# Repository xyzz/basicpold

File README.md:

You will need an SWD programmer for initial flashing. See https://github.com/xyzz/stm32f103-keyboard-bootloader for more info.

Known issues:
- PCB-mounted stabs don't quite line up with the plate
- PCB-mounted switches don't quite line up with the plate
- The mini-USB port doesn't extend far enough and the cable is quite loose.

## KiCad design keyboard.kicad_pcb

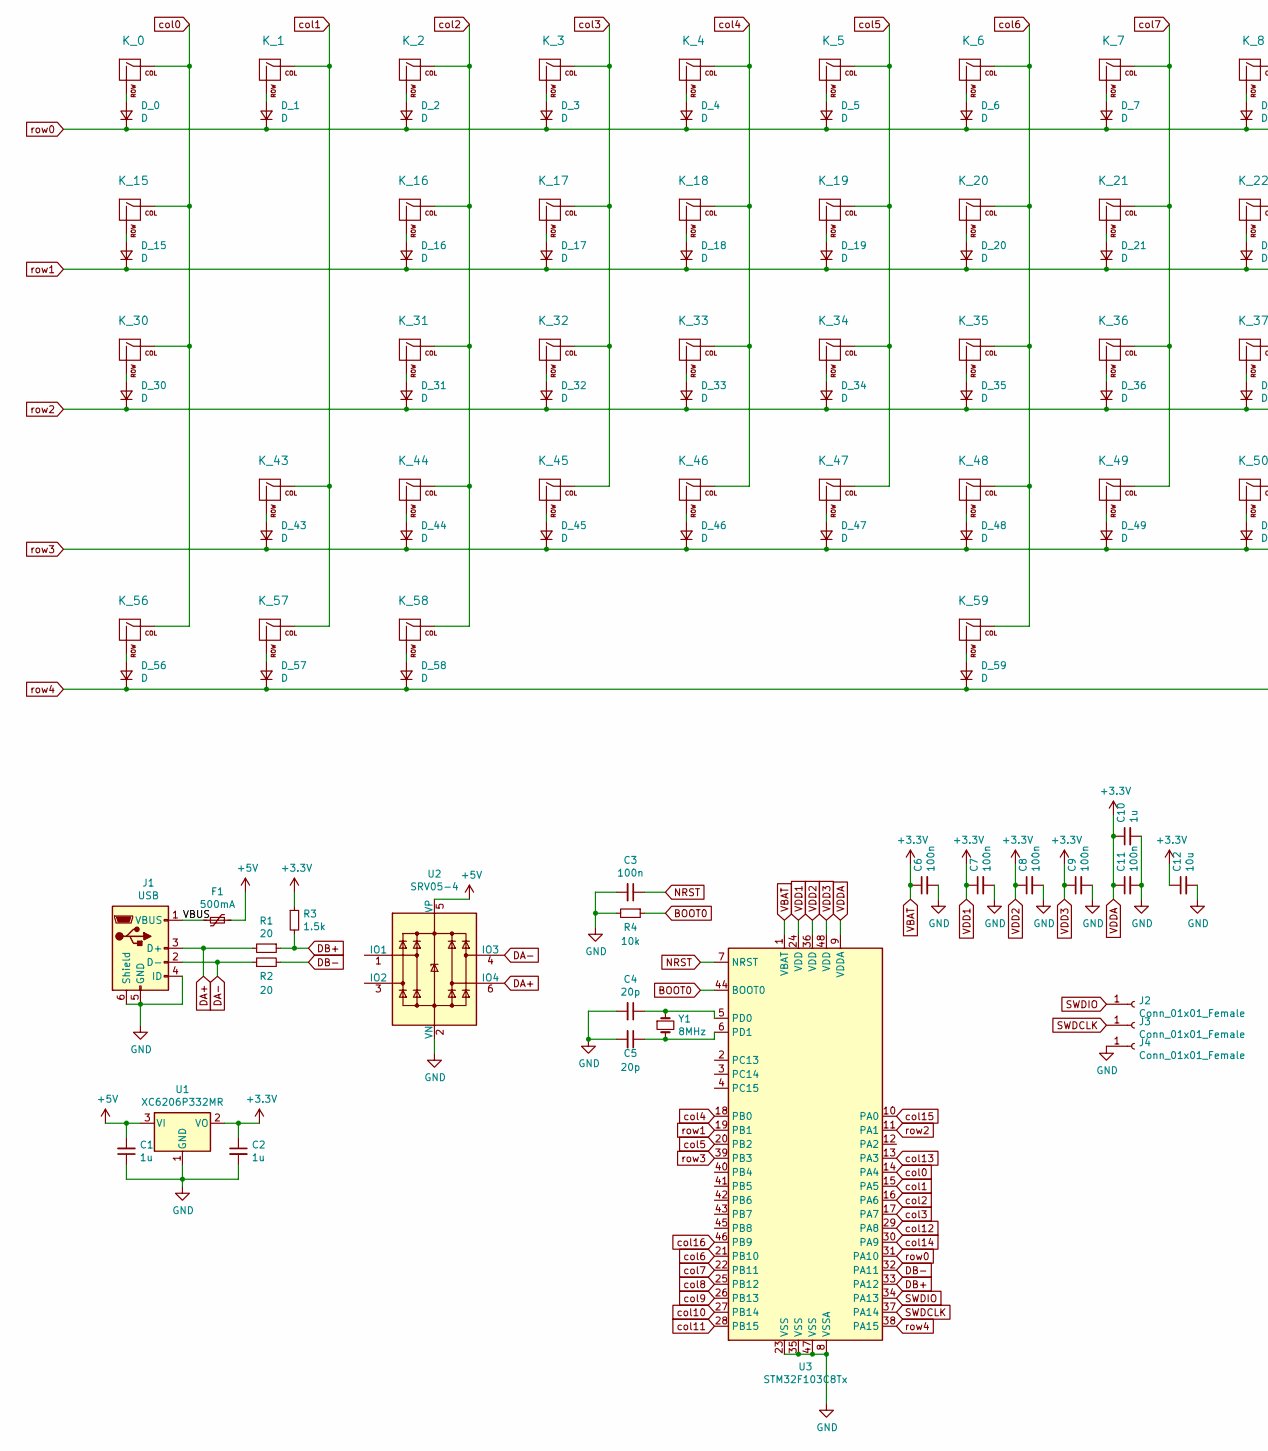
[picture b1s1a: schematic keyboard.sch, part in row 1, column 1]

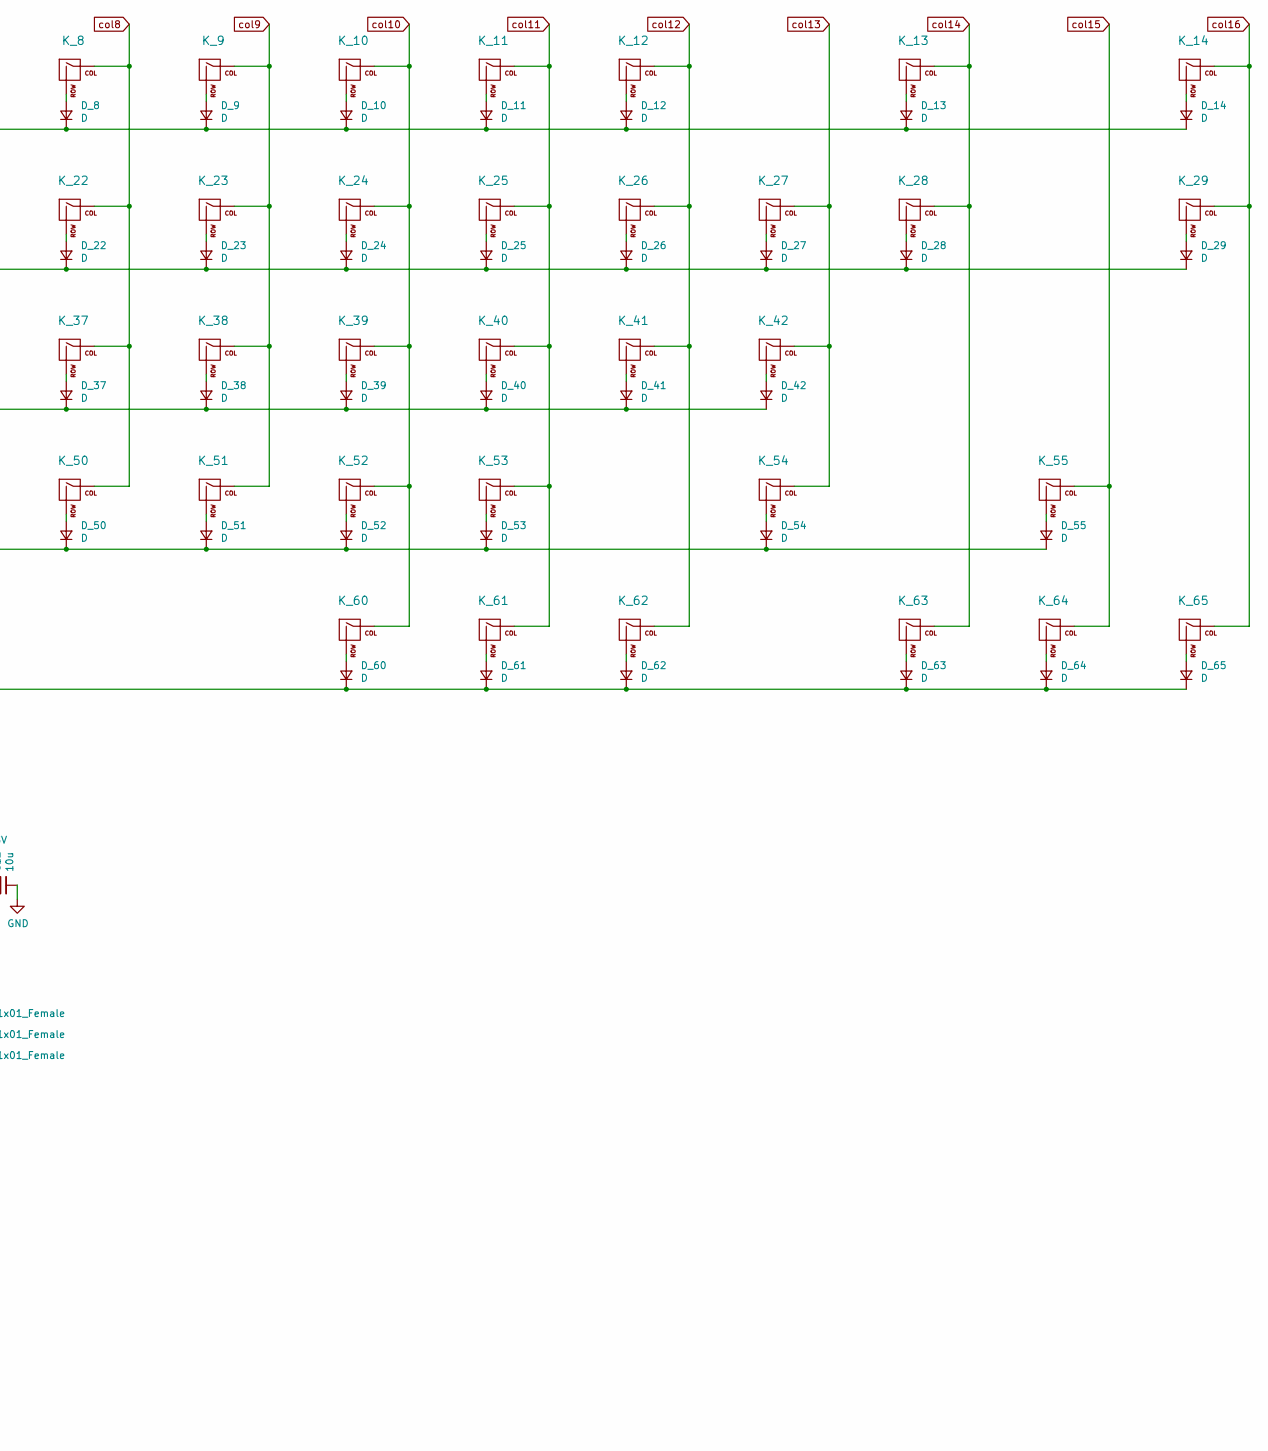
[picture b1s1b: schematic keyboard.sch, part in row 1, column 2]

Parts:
C1, C2, C10: 1u; C_0603_1608Metric; JLC C15849
C3, C6, C7, C8, C9, C11: 100n; C_0603_1608Metric; JLC C14663
C4, C5: 20p; C_0603_1608Metric; JLC C1648
C12: 10u; C_0603_1608Metric; JLC C19702
D_0, D_1, D_2, D_3, D_4, D_5, D_6, D_7, D_8, D_9, D_10, D_11, D_12, D_13, D_14, D_15, D_16, D_17, D_18, D_19, D_20, D_21, D_22, D_23, D_24, D_25, D_26, D_27, D_28, D_29, D_30, D_31, D_32, D_33, D_34, D_35, D_36, D_37, D_38, D_39, D_40, D_41, D_42, D_43, D_44, D_45, D_46, D_47, D_48, D_49, D_50, D_51, D_52, D_53, D_54, D_55, D_56, D_57, D_58, D_59, D_60, D_61, D_62, D_63, D_64, D_65: D; D_SOD-123; JLC C64898
F1: 500mA; Fuse_1206_3216Metric; JLC C369159
J1: USB; USB-Mini-B_ LCSC-C46398
J2, J3, J4: Conn_01x01_Female; TestPoint_Pad_D1.5mm
K_0, K_1, K_2, K_3, K_4, K_5, K_6, K_7, K_8, K_9, K_10, K_11, K_12, K_14, K_16, K_17, K_18, K_19, K_20, K_21, K_22, K_23, K_24, K_25, K_26, K_27, K_29, K_31, K_32, K_33, K_34, K_35, K_36, K_37, K_38, K_39, K_40, K_41, K_44, K_45, K_46, K_47, K_48, K_49, K_50, K_51, K_52, K_53, K_55, K_57, K_63, K_64, K_65: KEYSW; MXOnly-1U-NoLED
K_13: KEYSW; MXOnly-2U-NoLED
K_15, K_28: KEYSW; MXOnly-1.5U-NoLED
K_30: KEYSW; MXOnly-1.75U-NoLED
K_42, K_43, K_54: KEYSW; MXOnly-2.25U-NoLED
K_56, K_58, K_60, K_61, K_62: KEYSW; MXOnly-1.25U-NoLED
K_59: KEYSW; MXOnly-6.25U-ReversedStabilizers-NoLED
R1, R2: 20; R_0603_1608Metric; JLC C22950
R3: 1.5k; R_0603_1608Metric; JLC C22843
R4: 10k; R_0603_1608Metric; JLC C25804
U1: XC6206P332MR; SOT-23; JLC C5446
U2: SRV05-4; SOT-23-6; JLC C85364
U3: STM32F103C8Tx; LQFP-48_7x7mm_P0.5mm; JLC C8734
Y1: 8MHz; Crystal_SMD_5032-2Pin_5.0x3.2mm; JLC C115962

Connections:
+5V: C1.2, F1.1, U1.3 (VI), U2.5 (VP)
/VBUS: F1.2, J1.1 (VBUS)
BOOT0: R4.1, U3.44 (BOOT0)
DA+: J1.3 (D+), R1.2, U2.6 (IO4)
DA-: J1.2 (D-), R2.1, U2.4 (IO3)
DB+: R1.1, R3.2, U3.33 (PA12)
DB-: R2.2, U3.32 (PA11)
GND: C1.1, C2.2, C3.2, C4.2, C5.2, C6.2, C7.2, C8.2, C9.2, C10.2, C11.2, C12.2, J1.4 (ID), J1.5 (GND), J1.6 (Shield), J4.1, R4.2, U1.1 (GND), U2.2 (VN), U3.8 (VSSA), U3.23 (VSS), U3.35 (VSS), U3.47 (VSS)
NRST: C3.1, U3.7 (NRST)
unnamed: C4.1, U3.5 (PD0), Y1.1
unnamed: C5.1, U3.6 (PD1), Y1.2
unnamed: D_0.2 (A), K_0.2 (ROW)
unnamed: D_1.2 (A), K_1.2 (ROW)
unnamed: D_2.2 (A), K_2.2 (ROW)
unnamed: D_3.2 (A), K_3.2 (ROW)
unnamed: D_4.2 (A), K_4.2 (ROW)
unnamed: D_5.2 (A), K_5.2 (ROW)
unnamed: D_6.2 (A), K_6.2 (ROW)
unnamed: D_7.2 (A), K_7.2 (ROW)
unnamed: D_8.2 (A), K_8.2 (ROW)
unnamed: D_9.2 (A), K_9.2 (ROW)
unnamed: D_10.2 (A), K_10.2 (ROW)
unnamed: D_11.2 (A), K_11.2 (ROW)
unnamed: D_12.2 (A), K_12.2 (ROW)
unnamed: D_13.2 (A), K_13.2 (ROW)
unnamed: D_14.2 (A), K_14.2 (ROW)
unnamed: D_15.2 (A), K_15.2 (ROW)
unnamed: D_16.2 (A), K_16.2 (ROW)
unnamed: D_17.2 (A), K_17.2 (ROW)
unnamed: D_18.2 (A), K_18.2 (ROW)
unnamed: D_19.2 (A), K_19.2 (ROW)
unnamed: D_20.2 (A), K_20.2 (ROW)
unnamed: D_21.2 (A), K_21.2 (ROW)
unnamed: D_22.2 (A), K_22.2 (ROW)
unnamed: D_23.2 (A), K_23.2 (ROW)
unnamed: D_24.2 (A), K_24.2 (ROW)
unnamed: D_25.2 (A), K_25.2 (ROW)
unnamed: D_26.2 (A), K_26.2 (ROW)
unnamed: D_27.2 (A), K_27.2 (ROW)
unnamed: D_28.2 (A), K_28.2 (ROW)
unnamed: D_29.2 (A), K_29.2 (ROW)
unnamed: D_30.2 (A), K_30.2 (ROW)
unnamed: D_31.2 (A), K_31.2 (ROW)
unnamed: D_32.2 (A), K_32.2 (ROW)
unnamed: D_33.2 (A), K_33.2 (ROW)
unnamed: D_34.2 (A), K_34.2 (ROW)
unnamed: D_35.2 (A), K_35.2 (ROW)
unnamed: D_36.2 (A), K_36.2 (ROW)
unnamed: D_37.2 (A), K_37.2 (ROW)
unnamed: D_38.2 (A), K_38.2 (ROW)
unnamed: D_39.2 (A), K_39.2 (ROW)
unnamed: D_40.2 (A), K_40.2 (ROW)
unnamed: D_41.2 (A), K_41.2 (ROW)
unnamed: D_42.2 (A), K_42.2 (ROW)
unnamed: D_43.2 (A), K_43.2 (ROW)
unnamed: D_44.2 (A), K_44.2 (ROW)
unnamed: D_45.2 (A), K_45.2 (ROW)
unnamed: D_46.2 (A), K_46.2 (ROW)
unnamed: D_47.2 (A), K_47.2 (ROW)
unnamed: D_48.2 (A), K_48.2 (ROW)
unnamed: D_49.2 (A), K_49.2 (ROW)
unnamed: D_50.2 (A), K_50.2 (ROW)
unnamed: D_51.2 (A), K_51.2 (ROW)
unnamed: D_52.2 (A), K_52.2 (ROW)
unnamed: D_53.2 (A), K_53.2 (ROW)
unnamed: D_54.2 (A), K_54.2 (ROW)
unnamed: D_55.2 (A), K_55.2 (ROW)
unnamed: D_56.2 (A), K_56.2 (ROW)
unnamed: D_57.2 (A), K_57.2 (ROW)
unnamed: D_58.2 (A), K_58.2 (ROW)
unnamed: D_59.2 (A), K_59.2 (ROW)
unnamed: D_60.2 (A), K_60.2 (ROW)
unnamed: D_61.2 (A), K_61.2 (ROW)
unnamed: D_62.2 (A), K_62.2 (ROW)
unnamed: D_63.2 (A), K_63.2 (ROW)
unnamed: D_64.2 (A), K_64.2 (ROW)
unnamed: D_65.2 (A), K_65.2 (ROW)
SWDCLK: J3.1, U3.37 (PA14)
SWDIO: J2.1, U3.34 (PA13)
VBAT: C2.1, C6.1, C7.1, C8.1, C9.1, C10.1, C11.1, C12.1, R3.1, U1.2 (VO), U3.1 (VBAT), U3.9 (VDDA), U3.24 (VDD), U3.36 (VDD), U3.48 (VDD)
col0: K_0.1 (COL), K_15.1 (COL), K_30.1 (COL), K_56.1 (COL), U3.14 (PA4)
col1: K_1.1 (COL), K_43.1 (COL), K_57.1 (COL), U3.15 (PA5)
col2: K_2.1 (COL), K_16.1 (COL), K_31.1 (COL), K_44.1 (COL), K_58.1 (COL), U3.16 (PA6)
col3: K_3.1 (COL), K_17.1 (COL), K_32.1 (COL), K_45.1 (COL), U3.17 (PA7)
col4: K_4.1 (COL), K_18.1 (COL), K_33.1 (COL), K_46.1 (COL), U3.18 (PB0)
col5: K_5.1 (COL), K_19.1 (COL), K_34.1 (COL), K_47.1 (COL), U3.20 (PB2)
col6: K_6.1 (COL), K_20.1 (COL), K_35.1 (COL), K_48.1 (COL), K_59.1 (COL), U3.21 (PB10)
col7: K_7.1 (COL), K_21.1 (COL), K_36.1 (COL), K_49.1 (COL), U3.22 (PB11)
col8: K_8.1 (COL), K_22.1 (COL), K_37.1 (COL), K_50.1 (COL), U3.25 (PB12)
col9: K_9.1 (COL), K_23.1 (COL), K_38.1 (COL), K_51.1 (COL), U3.26 (PB13)
col10: K_10.1 (COL), K_24.1 (COL), K_39.1 (COL), K_52.1 (COL), K_60.1 (COL), U3.27 (PB14)
col11: K_11.1 (COL), K_25.1 (COL), K_40.1 (COL), K_53.1 (COL), K_61.1 (COL), U3.28 (PB15)
col12: K_12.1 (COL), K_26.1 (COL), K_41.1 (COL), K_62.1 (COL), U3.29 (PA8)
col13: K_27.1 (COL), K_42.1 (COL), K_54.1 (COL), U3.13 (PA3)
col14: K_13.1 (COL), K_28.1 (COL), K_63.1 (COL), U3.30 (PA9)
col15: K_55.1 (COL), K_64.1 (COL), U3.10 (PA0)
col16: K_14.1 (COL), K_29.1 (COL), K_65.1 (COL), U3.46 (PB9)
row0: D_0.1 (K), D_1.1 (K), D_2.1 (K), D_3.1 (K), D_4.1 (K), D_5.1 (K), D_6.1 (K), D_7.1 (K), D_8.1 (K), D_9.1 (K), D_10.1 (K), D_11.1 (K), D_12.1 (K), D_13.1 (K), D_14.1 (K), U3.31 (PA10)
row1: D_15.1 (K), D_16.1 (K), D_17.1 (K), D_18.1 (K), D_19.1 (K), D_20.1 (K), D_21.1 (K), D_22.1 (K), D_23.1 (K), D_24.1 (K), D_25.1 (K), D_26.1 (K), D_27.1 (K), D_28.1 (K), D_29.1 (K), U3.19 (PB1)
row2: D_30.1 (K), D_31.1 (K), D_32.1 (K), D_33.1 (K), D_34.1 (K), D_35.1 (K), D_36.1 (K), D_37.1 (K), D_38.1 (K), D_39.1 (K), D_40.1 (K), D_41.1 (K), D_42.1 (K), U3.11 (PA1)
row3: D_43.1 (K), D_44.1 (K), D_45.1 (K), D_46.1 (K), D_47.1 (K), D_48.1 (K), D_49.1 (K), D_50.1 (K), D_51.1 (K), D_52.1 (K), D_53.1 (K), D_54.1 (K), D_55.1 (K), U3.39 (PB3)
row4: D_56.1 (K), D_57.1 (K), D_58.1 (K), D_59.1 (K), D_60.1 (K), D_61.1 (K), D_62.1 (K), D_63.1 (K), D_64.1 (K), D_65.1 (K), U3.38 (PA15)

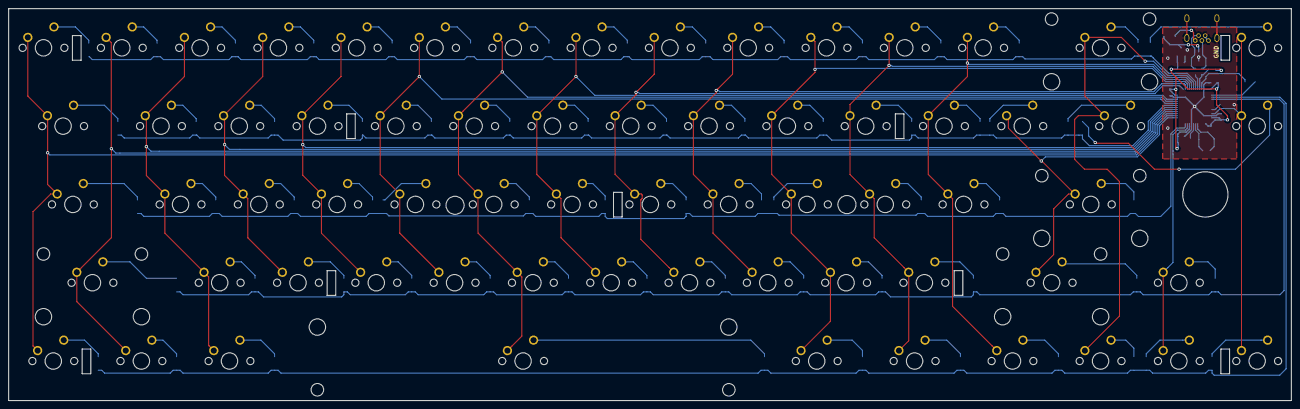
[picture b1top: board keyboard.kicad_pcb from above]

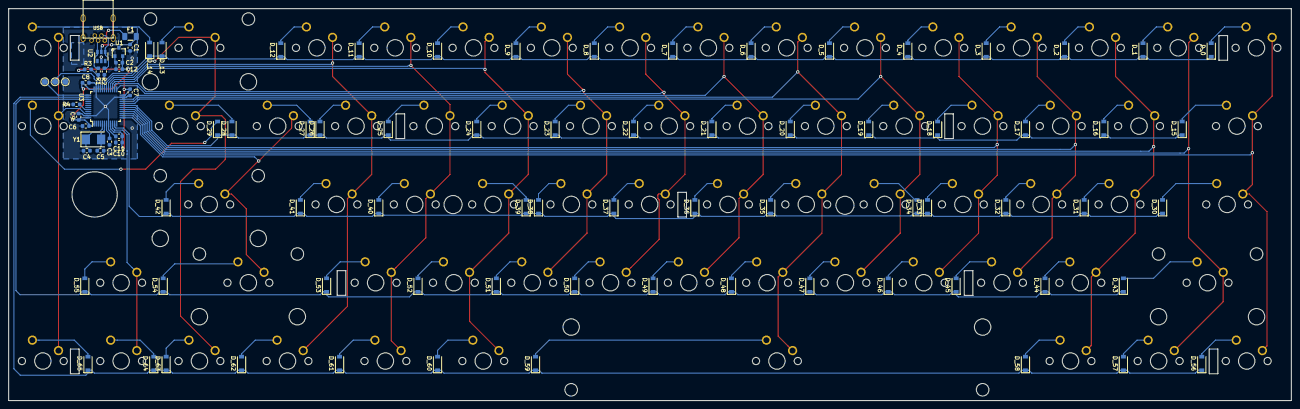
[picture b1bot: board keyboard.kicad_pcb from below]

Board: 2 copper layers, 311.8 x 95.2 mm, 157 parts (91 on the bottom side), 102 nets.

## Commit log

2020-01-29 initial
